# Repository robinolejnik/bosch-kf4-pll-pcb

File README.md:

# bosch_kf4_pll_pcb
PCB replacing the EPROM for controlling the PLL in a Bosch KF..4 radio

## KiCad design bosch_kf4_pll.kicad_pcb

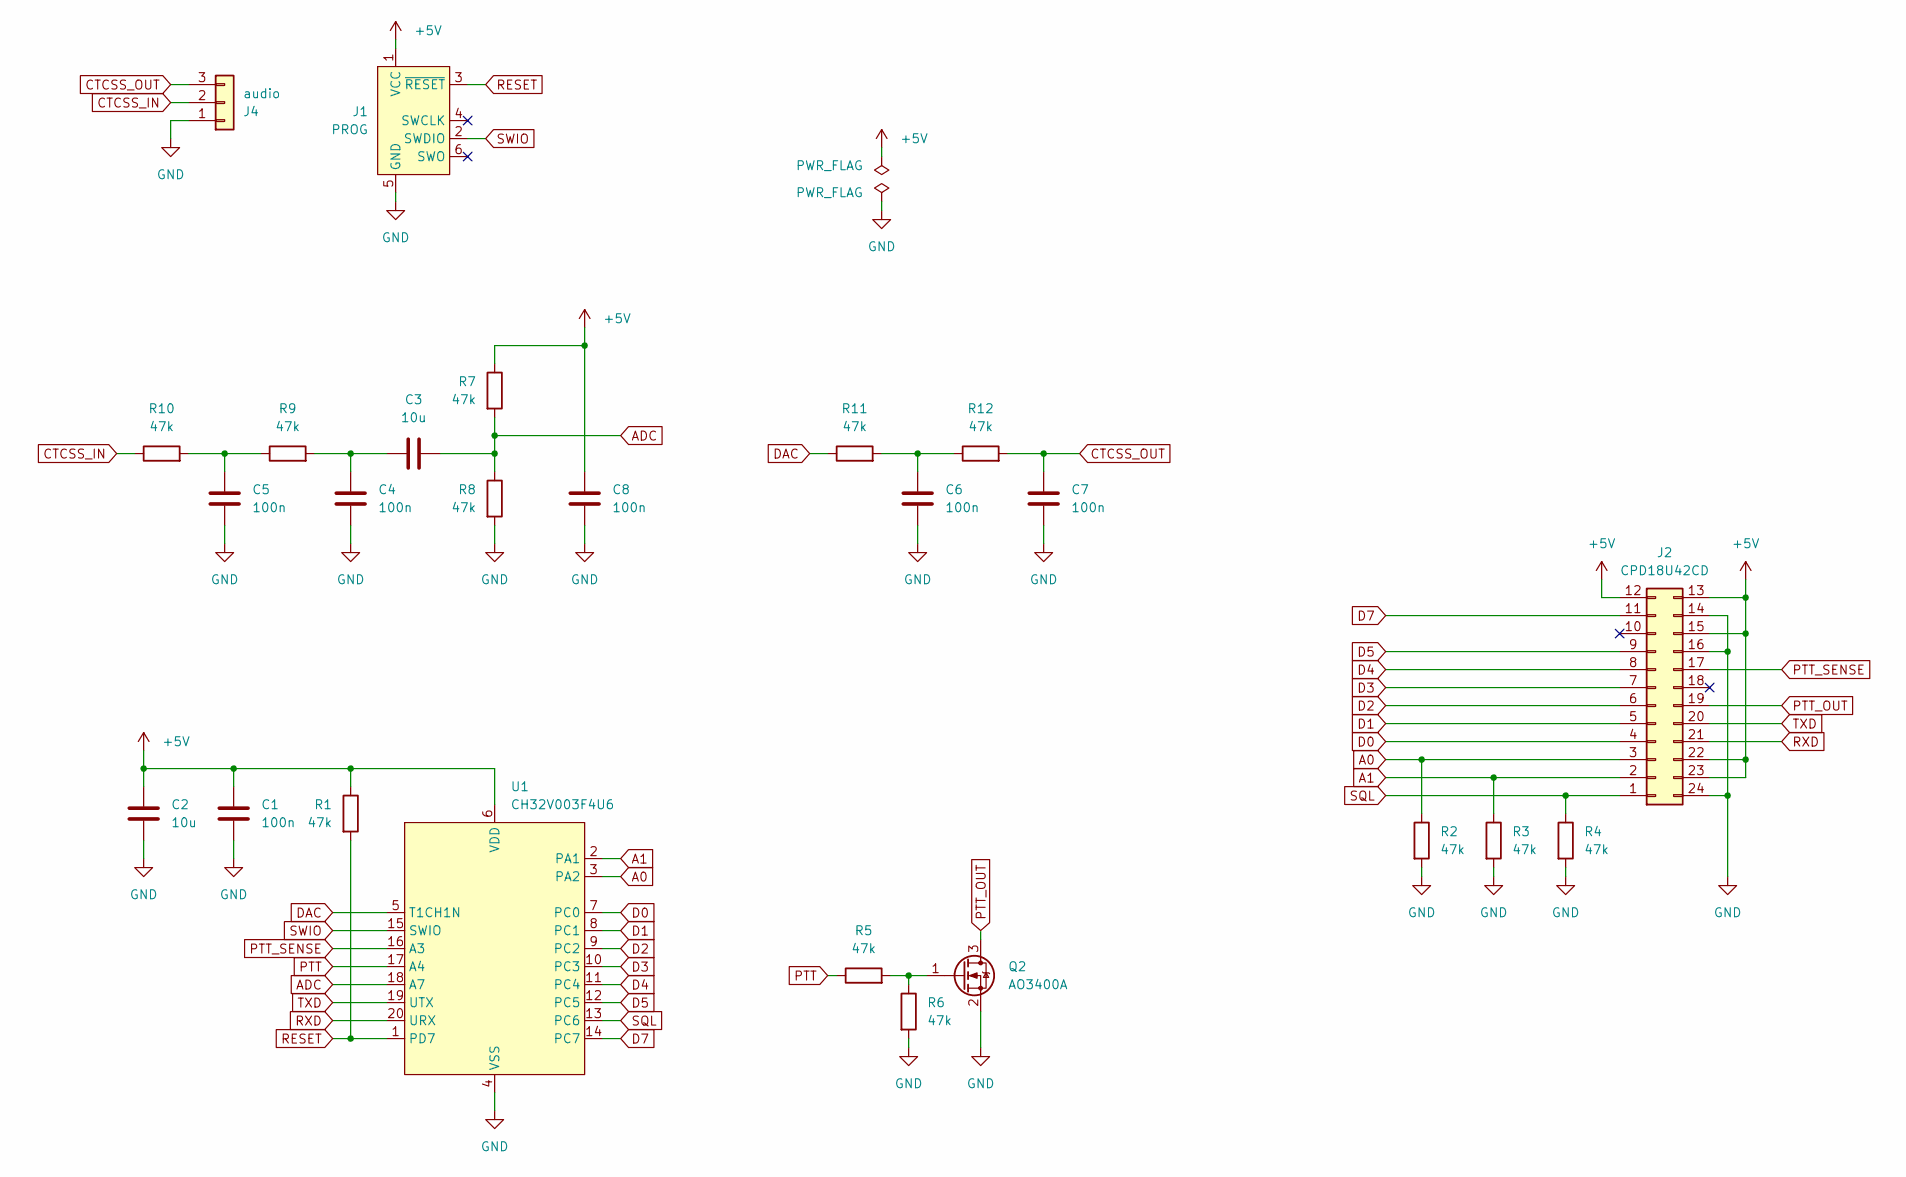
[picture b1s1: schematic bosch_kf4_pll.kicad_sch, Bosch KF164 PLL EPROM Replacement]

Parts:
C1, C4, C5, C6, C7, C8: 100n; C_0603_1608Metric
C2, C3: 10u; C_0603_1608Metric
J1: PROG; Tag-Connect_TC2030-IDC-FP_2x03_P1.27mm_Vertical
J2: CPD18U42CD; DIP-24_W15.24mm_Socket
J4: audio; PinHeader_1x03_P2.54mm_Vertical
Q2: AO3400A; SOT-23; MFR# AO3400A; LCSC# C344010
R1, R2, R3, R4, R5, R6, R7, R8, R9, R10, R11, R12: 47k; R_0603_1608Metric
U1: CH32V003F4U6; WQFN-20-1EP_3x3mm_P0.4mm_EP1.7x1.7mm

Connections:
+5V: C1.1, C2.1, C8.1, J1.1 (VCC), J2.12, J2.13, J2.15, J2.22, J2.23, R1.1, R7.1, U1.6 (VDD)
A0: J2.3, R2.1, U1.3 (PA2)
A1: J2.2, R3.1, U1.2 (PA1)
ADC: C3.2, R7.2, R8.1, U1.18 (A7)
CTCSS_IN: J4.2, R10.1
CTCSS_OUT: C7.1, J4.3, R12.2
D0: J2.4, U1.7 (PC0)
D1: J2.5, U1.8 (PC1)
D2: J2.6, U1.9 (PC2)
D3: J2.7, U1.10 (PC3)
D4: J2.8, U1.11 (PC4)
D5: J2.9, U1.12 (PC5)
D7: J2.11, U1.14 (PC7)
DAC: R11.1, U1.5 (T1CH1N)
GND: C1.2, C2.2, C4.2, C5.2, C6.2, C7.2, C8.2, J1.5 (GND), J2.14, J2.16, J2.24, J4.1, R2.2, R3.2, R4.2, R6.2, R8.2, U1.4 (VSS), U1.21 (VSS); also elsewhere on the board
unnamed: C3.1, C4.1, R9.2
unnamed: C5.1, R9.1, R10.2
unnamed: C6.1, R11.2, R12.1
unnamed 18: R5.2, R6.1; also elsewhere on the board
PTT: R5.1, U1.17 (A4)
PTT_OUT: J2.19; also elsewhere on the board
PTT_SENSE: J2.17, U1.16 (A3)
RESET: J1.3 (~RESET), R1.2, U1.1 (PD7)
RXD: J2.21, U1.20 (URX)
SQL: J2.1, R4.1, U1.13 (PC6)
SWIO: J1.2 (SWDIO), U1.15 (SWIO)
TXD: J2.20, U1.19 (UTX)

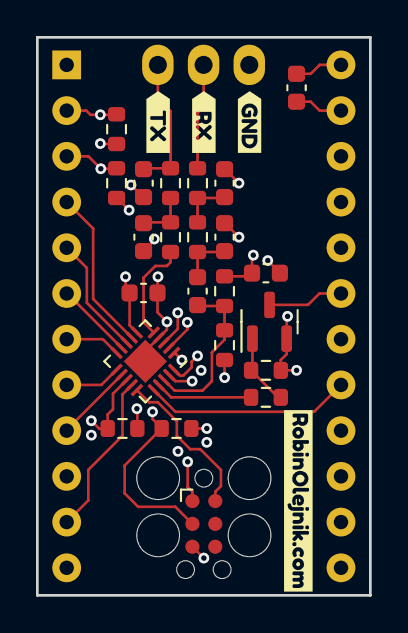
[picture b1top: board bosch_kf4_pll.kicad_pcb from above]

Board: 4 copper layers, 18.5 x 31.0 mm, 29 parts (0 on the bottom side), 27 nets.

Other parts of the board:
Q1: AO3400A; SOT-23
kibuzzard-655EAB0A: G***; kibuzzard-655EAB0A
kibuzzard-655EABBF: G***; kibuzzard-655EABBF
kibuzzard-655EABCC: G***; kibuzzard-655EABCC
kibuzzard-655EABEF: G***; kibuzzard-655EABEF

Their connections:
GND: Q1.2 (S); also elsewhere on the board
unnamed 18: Q1.1 (G); also elsewhere on the board
PTT_OUT: Q1.3 (D); also elsewhere on the board

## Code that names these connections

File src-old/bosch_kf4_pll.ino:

#include "uart.h"
#include "util/delay.h"

// ##### Hardware #####
#define PTT_SENSE_DDR   DDRD
#define PTT_SENSE_PORT  PORTD
#define PTT_SENSE_PIN   PIND
#define PTT_SENSE_BIT   PD2

#define PTT_OUT_DDR     DDRC
#define PTT_OUT_PORT    PORTC
#define PTT_OUT_BIT     PC5

// ##### Config #####
#define UART_BAUD_RATE 38400

//#define F_MOD 16800000  // Simplex
//#define F_MOD 21400000  // (Semi-)Duplex SU
#define F_MOD 26000000  // (Semi-)Duplex SO

#define REPEATERTIMEOUT 30

#define F_UPDATE 50000
#define F_UPDATE_RPT 10

/*
prom      Platine AVR Arduino function
04 D0     -       PC1 A1
05 D1     -       PC0 A0
06 D2     -       PB5 13
07 D3     -       PB4 12
08 D4     -       PB0 8       ub/ob
09 D5     4       PD7 7
10 D6     3       PD6 6       über K22 nach St III /4 Leistungsumschaltung
11 D7     2       PD5 5       K19

17 A7     -       PD3 3       ptt sense
-


00  PD0 21  RXD
01  PD1 20  TXD
02  PD2 19  SQL
03  PD3 17  ptt sense
04  PD4 nc
05  PD5 11  D7
06  PD6 10  D6
07  PD7 09  D5
08  PB0 08  D4
09  PB1 -   PWM A
10  PB2 -   PWM B
11  PB3 nc
12  PB4 07  D3
13  PB5 06  D2
A0  PC0 05  D1
A1  PC1 04  D0
A2  PC2 03  A0
A3  PC3 02  A1
A4  PC4 01  A
A5  PC5 18  PTT

ddr
B 0011 0110
C 0010 0011
D 1110 00xx
*/

uint8_t SINE_TABLE[]= {
  128, 131, 134, 137, 140, 143, 146, 149, 152, 156, 159, 162, 165, 168, 171, 174,
  176, 179, 182, 185, 188, 191, 193, 196, 199, 201, 204, 206, 209, 211, 213, 216,
  218, 220, 222, 224, 226, 228, 230, 232, 234, 236, 237, 239, 240, 242, 243, 245,
  246, 247, 248, 249, 250, 251, 252, 252, 253, 254, 254, 255, 255, 255, 255, 255,
  255, 255, 255, 255, 255, 255, 254, 254, 253, 252, 252, 251, 250, 249, 248, 247,
  246, 245, 243, 242, 240, 239, 237, 236, 234, 232, 230, 228, 226, 224, 222, 220,
  218, 216, 213, 211, 209, 206, 204, 201, 199, 196, 193, 191, 188, 185, 182, 179,
  176, 174, 171, 168, 165, 162, 159, 156, 152, 149, 146, 143, 140, 137, 134, 131,
  127, 124, 121, 118, 115, 112, 109, 106, 103, 99, 96, 93, 90, 87, 84, 81,
  79, 76, 73, 70, 67, 64, 62, 59, 56, 54, 51, 49, 46, 44, 42, 39,
  37, 35, 33, 31, 29, 27, 25, 23, 21, 19, 18, 16, 15, 13, 12, 10,
  9, 8, 7, 6, 5, 4, 3, 3, 2, 1, 1, 0, 0, 0, 0, 0,
  0, 0, 0, 0, 0, 0, 1, 1, 2, 3, 3, 4, 5, 6, 7, 8,
  9, 10, 12, 13, 15, 16, 18, 19, 21, 23, 25, 27, 29, 31, 33, 35,
  37, 39, 42, 44, 46, 49, 51, 54, 56, 59, 62, 64, 67, 70, 73, 76,
  79, 81, 84, 87, 90, 93, 96, 99, 103, 106, 109, 112, 115, 118, 121, 124
};
uint16_t phaseRegA, phaseIncA;
uint16_t phaseRegB, phaseIncB;

uint8_t data[8];

volatile uint32_t repeaterTimer;
uint8_t repeaterStatus;

void setrxfreq(const char* s) {
  uint32_t n = 0;
  while(*s!=0) {
    n *= 10;
    n += *s++ - 48;
  }
  n -= 21400000;
  if(n % 12500==0) {
    data[0] |= 0xA0;
    data[1] |= 0xA0;
    data[2] |= 0xA0;
    data[3] |= 0xA0;
    n /= 12500;
  }
  else if(n % 10000==0) {
    data[0] |= 0xB0;
    data[1] |= 0xB0;
    data[2] |= 0xB0;
    data[3] |= 0xB0;
    n /= 10000;
  }
  if(n>=25600) {
    data[2] |= 0x08;
    n-=25600;
  }
  if(n>=12800) {
    data[2] |= 0x04;
    n-=12800;
  }
  if(n>=6400) {
    data[2] |= 0x02;
    n-=6400;
  }
  if(n>=3200) {
    data[2] |= 0x01;
    n-=3200;
  }
  if(n>=1600) {
    data[3] |= 0x08;
    n-=1600;
  }
  if(n>=800) {
    data[3] |= 0x04;
    n-=800;
  }
  if(n>=400) {
    data[3] |= 0x02;
    n-=400;
  }
  if(n>=200) {
    data[3] |= 0x01;
    n-=200;
  }
  if(n>=100) {
    data[1] |= 0x08;
    n-=100;
  }
  if(n>=64) {
    data[1] |= 0x04;
    n-=64;
  }
  if(n>=32) {
    data[1] |= 0x02;
    n-=32;
  }
  if(n>=16) {
    data[1] |= 0x01;
    n-=16;
  }
  if(n>=8) {
    data[0] |= 0x08;
    n-=8;
  }
  if(n>=4) {
    data[0] |= 0x04;
    n-=4;
  }
  if(n>=2) {
    data[0] |= 0x02;
    n-=2;
  }
  if(n>=1) {
    data[0] |= 0x01;
    n-=1;
  }
}

void settxfreq(const char* s) {
  uint32_t n = 0;
  while(*s!=0) {
    n *= 10;
    n += *s++ - 48;
  }
  n -= F_MOD;          // 172780000 155980000
  if(n % 12500==0) {
    data[4] |= 0xA0;
    data[5] |= 0xA0;
    data[6] |= 0xA0;
    data[7] |= 0xA0;
    n /= 12500;
  }
  else if(n % 10000==0) {
    data[4] |= 0xB0;
    data[5] |= 0xB0;
    data[6] |= 0xB0;
    data[7] |= 0xB0;
    n /= 10000;
  }
  if(n>=25600) {
    data[6] |= 0x08;
    n-=25600;
  }
  if(n>=12800) {
    data[6] |= 0x04;
    n-=12800;
  }
  if(n>=6400) {
    data[6] |= 0x02;
    n-=6400;
  }
  if(n>=3200) {
    data[6] |= 0x01;
    n-=3200;
  }
  if(n>=1600) {
    data[7] |= 0x08;
    n-=1600;
  }
  if(n>=800) {
    data[7] |= 0x04;
    n-=800;
  }
  if(n>=400) {
    data[7] |= 0x02;
    n-=400;
  }
  if(n>=200) {
    data[7] |= 0x01;
    n-=200;
  }
  if(n>=100) {
    data[5] |= 0x08;
    n-=100;
  }
  if(n>=64) {
    data[5] |= 0x04;
    n-=64;
  }
  if(n>=32) {
    data[5] |= 0x02;
    n-=32;
  }
  if(n>=16) {
    data[5] |= 0x01;
    n-=16;
  }
  if(n>=8) {
    data[4] |= 0x08;
    n-=8;
  }
  if(n>=4) {
    data[4] |= 0x04;
    n-=4;
  }
  if(n>=2) {
    data[4] |= 0x02;
    n-=2;
  }
  if(n>=1) {
    data[4] |= 0x01;
    n-=1;
  }
  
}

int main(void) {
  uint8_t repeaterStatus = 0;

  DDRB |= (1<<PB5) | (1<<PB4) | (1<<PB2) | (1<<PB1);
  DDRC |= (1<<PC5) | (1<<PC1) | (1<<PC0);
  DDRD |= (1<<PD7) | (1<<PD6) | (1<<PD5);
  PTT_SENSE_PORT |= (1<<PTT_SENSE_BIT);

  TCCR1A = (1<<WGM11) | (1<<WGM10) | (1<<COM1A1) | (1<<COM1B1);
  TCCR1B = (1<<CS10);
  OCR1A = 0;
  OCR1B = 0;
/*
  TCCR2A = (1<<WGM21);
  TCCR2B = (1<<CS21);
  OCR2A = (F_CPU / 8 / F_UPDATE - 1);
  TIMSK2 = (1<<OCIE2A);
*/

  TCCR0A = (1<<WGM01);
  TCCR0B = (1<<CS02) | (1<<CS00);
  OCR0A = 255;//(F_CPU / 1024 / 256 - 1);
  TIMSK0 = (1<<OCIE0A);
  
  // enable pin change interrupt for address input
  //PCMSK1 = (1<<PCINT9) | (1<PCINT8);
  //PCICR = (1<<PCIE1);

  phaseIncA = 2000 * 65536 / F_UPDATE;
  phaseIncB = 500 * 65536 / F_UPDATE;

  uart_init();
  sei();
  uart_putc('S');

  setrxfreq("145737500");
  settxfreq("145137500");
  
  while(1) {
    if(!(PTT_SENSE_PIN & (1<<PTT_SENSE_BIT))) {    // senden
      PTT_OUT_PORT |= (1<<PTT_OUT_BIT);
      repeaterStatus = 1;
    }
    if(repeaterStatus==1 && (PTT_SENSE_PIN & (1<<PTT_SENSE_BIT))) {  // nachlauf
      repeaterStatus = 2;
      repeaterTimer = 0;
      uart_putc(2);
    }
    if(repeaterStatus==2 && repeaterTimer>=90) {
      PTT_OUT_PORT &= ~(1<<PTT_OUT_BIT);
      repeaterStatus = 0;
      uart_putc(0);
    }

    uint8_t address = ((PINC >> 2) & 0x03) | ((PIND >> 1) & 0x04);
    PORTB &= ((data[address] << 3) & (1<<PB5)) | ((data[address] << 1) & (1<<PB4)) | ((data[address] >> 4) & (1<<PB0)) | ~((1<<PB5) | (1<<PB4) | (1<<PB0));
    PORTB |= ((data[address] << 3) & (1<<PB5)) | ((data[address] << 1) & (1<<PB4)) | ((data[address] >> 4) & (1<<PB0));
    PORTC &= ((data[address] << 1) & (1<<PC1)) | ((data[address] >> 1) & (1<<PC0)) | ~((1<<PC1) | (1<<PC0));
    PORTC |= ((data[address] << 1) & (1<<PC1)) | ((data[address] >> 1) & (1<<PC0));
    PORTD &= ((data[address] << 2) & (1<<PD7)) |  (data[address]       & (1<<PD6)) | ((data[address] >> 2) & (1<<PD5)) | ~((1<<PD7) | (1<<PD6) | (1<<PD5));
    PORTD |= ((data[address] << 2) & (1<<PD7)) |  (data[address]       & (1<<PD6)) | ((data[address] >> 2) & (1<<PD5));
    
  }
  return 0;
}

ISR(TIMER0_COMPA_vect) {
  repeaterTimer++;
}

ISR(TIMER2_COMPA_vect) {
  /*
  uint8_t address = ((PINC >> 2) & 0x03) | ((PIND >> 1) & 0x04);
    PORTB &= ((data[address] << 3) & (1<<PB5)) | ((data[address] << 1) & (1<<PB4)) | ((data[address] >> 4) & (1<<PB0)) | ~((1<<PB5) | (1<<PB4) | (1<<PB0));
    PORTB |= ((data[address] << 3) & (1<<PB5)) | ((data[address] << 1) & (1<<PB4)) | ((data[address] >> 4) & (1<<PB0));
    PORTC &= ((data[address] << 1) & (1<<PC1)) | ((data[address] >> 1) & (1<<PC0)) | ~((1<<PC1) | (1<<PC0));
    PORTC |= ((data[address] << 1) & (1<<PC1)) | ((data[address] >> 1) & (1<<PC0));
    PORTD &= ((data[address] << 2) & (1<<PD7)) |  (data[address]       & (1<<PD6)) | ((data[address] >> 2) & (1<<PD5)) | ~((1<<PD7) | (1<<PD6) | (1<<PD5));
    PORTD |= ((data[address] << 2) & (1<<PD7)) |  (data[address]       & (1<<PD6)) | ((data[address] >> 2) & (1<<PD5));
    */
    /*
  phaseRegA += phaseIncA;
  phaseRegB += phaseIncB;
  OCR1A = SINE_TABLE[(uint8_t)(phaseRegA >> 8)];
  OCR1B = SINE_TABLE[(uint8_t)(phaseRegB >> 8)];
  //repeaterTimer++;
  */
}


ISR(PCINT1_vect) {
}


/*
PORTB xx23 xxx4
PORTC xxxx xx01
PORTD 567x xxxx

0 PC1 << 1
1 PC0 >> 1
2 PB5 << 3 x
3 PB4 << 1 x
4 PB0 >> 4 x
5 PD7 << 2
6 PD6 
7 PD5 >> 2
*/

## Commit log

2018-08-23 First, faulty version of pcb
2018-09-15 Updated schematic and pcb to new version.
2018-10-07 Removed last DRC errors
2022-06-09 Added arduino sketch
2023-11-17 PCB remake with WCH CH32V003 controller
2023-11-18 Added CTCSS filters
2023-11-23 Finalized Rev2, added gerbers and PDF schematic
